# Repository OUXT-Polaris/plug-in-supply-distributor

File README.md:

# plug-in-supply-distributor

## Overview

This is one of the boards under development by OUXT for the RobotX competition. It is part of the power supply system for the controller, and has connector interlocking, simple reverse voltage protection, fuse monitoring and external input functions.

KiCAD ( https://www.kicad.org/ ) is used for circuit design and PCB layout.

## CAD

### Version

KiCAD 5.1.7

### Parts Library

The symbol libraries and footprint libraries used in this schematic and PCB layout are basically KiCAD standard libraries, but some of them are in the following repositories.

https://github.com/alnicomag/kicad-custom-lib

## PCB rendering images

## Schematics

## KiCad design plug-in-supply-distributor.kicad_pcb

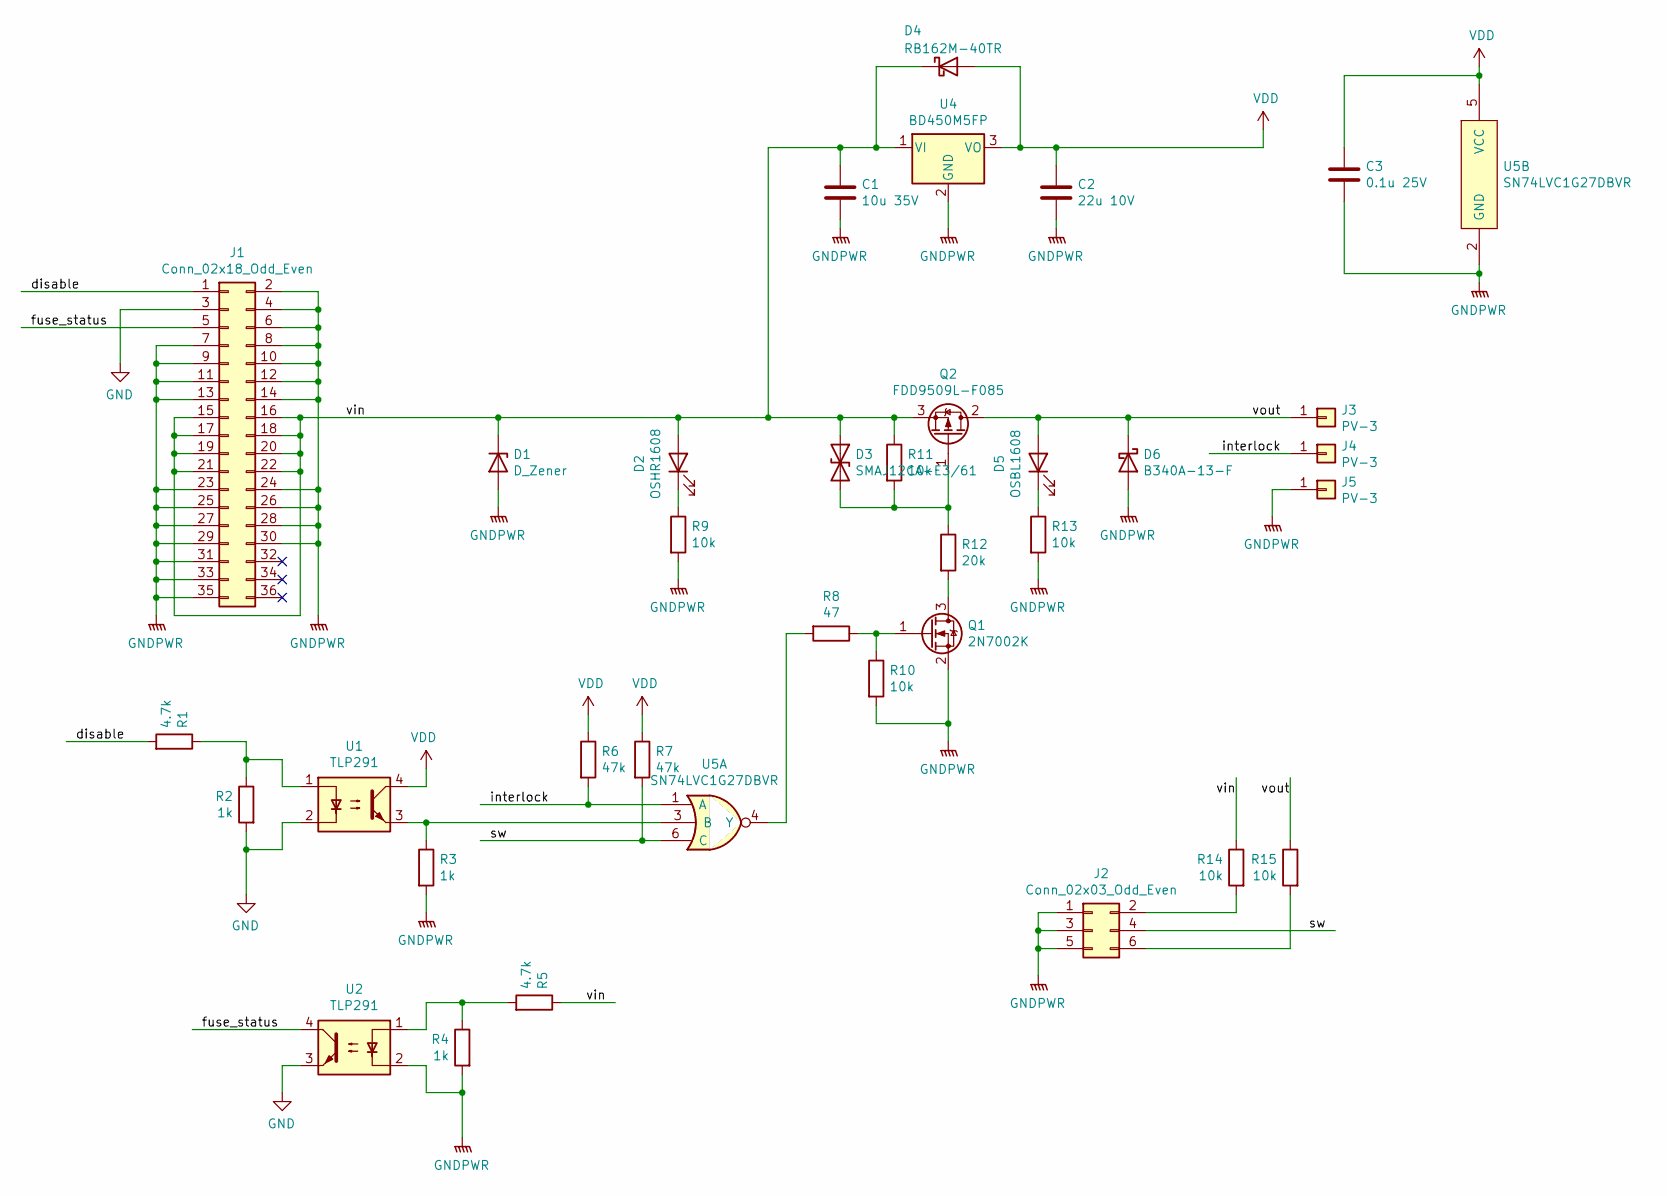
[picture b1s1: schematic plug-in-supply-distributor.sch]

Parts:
C1: 10u 35V; C_0805_2012Metric_Pad1.18x1.45mm_HandSolder
C2: 22u 10V; C_1206_3216Metric_Pad1.42x1.75mm_HandSolder
C3: 0.1u 25V; C_0603_1608Metric_Pad1.08x0.95mm_HandSolder
D1: D_Zener; D_SMC
D2: OSHR1608; LED_0603_1608Metric_Pad1.05x0.95mm_HandSolder
D3: SMAJ12CA-E3/61; D_SMA
D4: RB162M-40TR; D_SOD-123
D5: OSBL1608; LED_0603_1608Metric_Pad1.05x0.95mm_HandSolder
D6: B340A-13-F; D_SMA
J1: Conn_02x18_Odd_Even; TEConnectivity_2-5530843-7_card-edge
J2: Conn_02x03_Odd_Even; PinHeader_2x03_P2.54mm_Horizontal
J3, J5: PV-3; PV-3_via
J4: PV-3
Q1: 2N7002K; SOT-23
Q2: FDD9509L-F085; TO-252-2
R1, R5: 4.7k; R_0603_1608Metric_Pad1.05x0.95mm_HandSolder
R2, R3, R4: 1k; R_0603_1608Metric_Pad1.05x0.95mm_HandSolder
R6, R7: 47k; R_0603_1608Metric_Pad1.05x0.95mm_HandSolder
R8: 47; R_0603_1608Metric_Pad1.05x0.95mm_HandSolder
R9, R10, R11, R13, R14, R15: 10k; R_0603_1608Metric_Pad1.05x0.95mm_HandSolder
R12: 20k; R_0603_1608Metric_Pad1.05x0.95mm_HandSolder
U1, U2: TLP291; SOIC-4_4.55x2.6mm_P1.27mm
U4: BD450M5FP; TO-252-2
U5: SN74LVC1G27DBVR; SOT-23-6

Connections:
/disable: J1.1, R1.2
/fuse_status: J1.5, U2.4
/interlock: J4.1, R6.2, U5.1 (A)
/sw: J2.4, R7.2, U5.6 (C)
/vin: C1.1, D1.1 (K), D2.2 (A), D3.1 (A1), D4.1 (K), J1.15, J1.16, J1.17, J1.18, J1.19, J1.20, J1.21, J1.22, Q2.3 (S), R5.1, R11.1, R14.1, U4.1 (VI)
/vout: D5.2 (A), D6.1 (K), J3.1, Q2.2 (D), R15.1
GND: J1.3, R2.2, U1.2, U2.3
GNDPWR: C1.2, C2.2, C3.2, D1.2 (A), D6.2 (A), J1.2, J1.4, J1.6, J1.7, J1.8, J1.9, J1.10, J1.11, J1.12, J1.13, J1.14, J1.23, J1.24, J1.25, J1.26, J1.27, J1.28, J1.29, J1.30, J1.31, J1.33, J1.35, J2.1, J2.3, J2.5, J5.1, Q1.2 (S), R3.2, R4.2, R9.2, R10.2, R13.2, U2.2, U4.2 (GND), U5.2 (GND)
unnamed: D2.1 (K), R9.1
unnamed: D3.2 (A2), Q2.1 (G), R11.2, R12.1
unnamed: D5.1 (K), R13.1
unnamed: J2.2, R14.2
unnamed: J2.6, R15.2
unnamed: Q1.1 (G), R8.1, R10.1
unnamed: Q1.3 (D), R12.2
unnamed: R1.1, R2.1, U1.1
unnamed: R3.1, U1.3, U5.3 (B)
unnamed: R4.1, R5.2, U2.1
unnamed: R8.2, U5.4 (Y)
VDD: C2.1, C3.1, D4.2 (A), R6.1, R7.1, U1.4, U4.3 (VO), U5.5 (VCC)

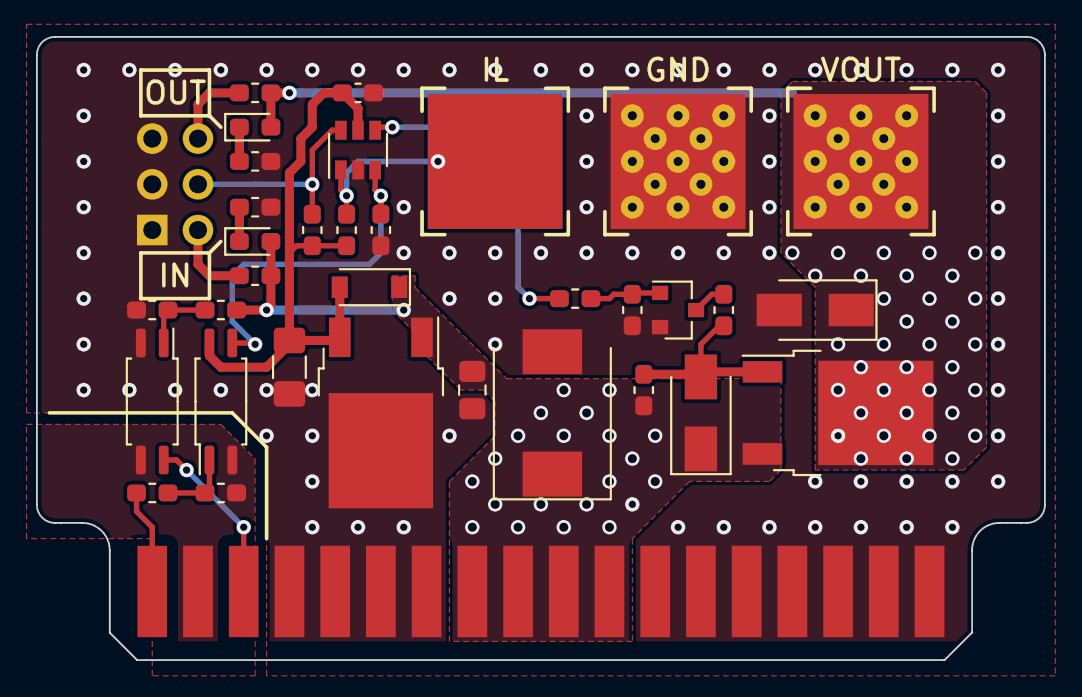
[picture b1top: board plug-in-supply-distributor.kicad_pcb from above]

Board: 2 copper layers, 56.0 x 34.6 mm, 35 parts (1 on the bottom side), 20 nets.

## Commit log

2021-06-17 Add kicad files
2021-06-17 Add pcb images
2021-06-22 Add library table
2021-06-22 Update pcb layout
2021-06-23 Update schematics and pcb layout
2021-06-23 Add lib cache file
2021-07-16 Update kicad files
2021-07-29 Update schematics
2021-07-29 Update images for README
